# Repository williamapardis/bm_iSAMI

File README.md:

# iSAMI Bristlemouth Interface Firmware
This includes the firmware for the Bristlemouth development kit to interface a Sofar Smart Spotter Mooring with Sunburst Sensor's iSAMI-pH instrument. The frimware functions as follows:

* Bristlemouth Mote triggers a measurement on the iSAMI through the RS232 connection at a specified interval.
* The iSAMI runs through its measurment sequence (~60s) and transmits its raw hex data through the RS232 connection.
* This 233 byte hex code is proccessed and a series of calculations lead to the determination of pH.
* Raw hex data is stored on the Spotter SD card through the Bristlemouth network
* pH and external temperature are stored on the Spotter SD and transmitted over the cellular modem.

Check out the project on the [forum](https://bristlemouth.discourse.group/t/turn-key-coastal-ph-monitoring-with-spotter-bristlemouth-and-sunburst-sensor-s-isami-ph/489?u=wpardis).

## Dependencies
### Main Protocol
- BM Protocol v2.1.0
  - Repository: https://github.com/bristlemouth/bm_protocol.git

## Wiring of the iSAMI-pH to the Bristlemouth Dev Kit
Please note that I have secured the development board to the oposite endcap it comes pre installed on with the Dev. Kit. This lets us utilize the 2P Molex Microfit interconnect for assembly of the pressure vessel, rather than adding our own.
| Pin to Pin Discription | Example Image of termination |
|---------|---------|
| | |

# The Project
We're trying to put powerful chemistry in the hands of a wider demographic and lower the barrier to entry through standardized integration of well established oceanographic assets. 

This is the integration and deomonstraition of Sunburst Sensor’s iSAMI-pH and Sofar Ocean’s Smart Spotter Buoy through the Bristlemouth Dev. kit. The Spotter and the iSAMI are well paired economically/electromechanically. However, the high cost of custom engineering integration still limits these cost effective solutions. With the adoption of Bristlemouth we mitigate costly integration. This strategic development has the opportunity to open up coastal pH monitoring to a wider range of users through the turn-key operability of Sofar’s ecosystem. This ecosystem as a gateway to the demonstrated success of Sunburst Sensor’s spectrophotometric measurement approach enables a higher density of accurate and low drift pH observations in the ocean.

## How does the iSAMI-pH work?
Most people are familiar with litmus paper—strips containing pH-sensitive dye that change color when exposed to different solutions. The iSAMI-pH is essentially an automated version of litmus paper, but instead of visual observation, it mixes liquid dye with seawater and analyzes the color change using precise embedded optical electronics. We would call this a spectrophotometric pH method: spectro - (color), photo - (light), metric - (measuring). Here is the dye (m-Cresol Purple) in action:

The advantage of spectrophotometric pH is that, rather than taking a calibrated approach like electrodes, it directly measures hydrogen ions in solution. measure of hydrogen ions in solution. This calibration free method consequently has very low drift, allowing these sensors to dwell for years while maintaining their accuracy.
Thanks to the exacting work of analytical chemists, this dye’s physical properties have been scrutinized in the seawater matrix, making it highly accurate. It is considered the gold standard for quantitative oceanographic pH measurement.

Thanks to Sunburst Sensor’s engineering and attention to detail, we have instruments like the iSAMI-pH, which realistically bring this measurement into the real world ocean environment. Here is a nice [overview of Sunburst](https://youtu.be/aXZPkW4L6uA?si=S3U1Ic4FXqChgCz4) as they were working to compete in the Wendy Schmidt Ocean-X prize. An important note [Sunburst Sensor took first place](https://www.pmel.noaa.gov/news-story/wendy-schmidt-ocean-health-xprize-winners-announced#:~:text=Winning%20first%20place%20in%20both,each%20team%20took%20home%20%24250%2C000.) in both categories: Accuracy and affordability. 

## Why pH?
If you were to take a single drop of seawater from the central pacific and compare it to one 30 years ago there would be ~42 billion more hydrogen ions in that single drop. Increased carbon dioxide in our atmosphere reacts with our ocean producing hydrogen ions in solution and perturbing our ocean's fundamental chemistry. How do we conceptualize such large changes in hydrogen ion concentration? The practical answer is pH. pH compresses the wild extremes of hydrogen ion concentration into a tidy, 14-step logarithmic scale.

$$
pH = log_{10}([H^+]),\ \ \ \ [H^+] \equiv \text{Hydtrogen Ion Concentraition}
$$

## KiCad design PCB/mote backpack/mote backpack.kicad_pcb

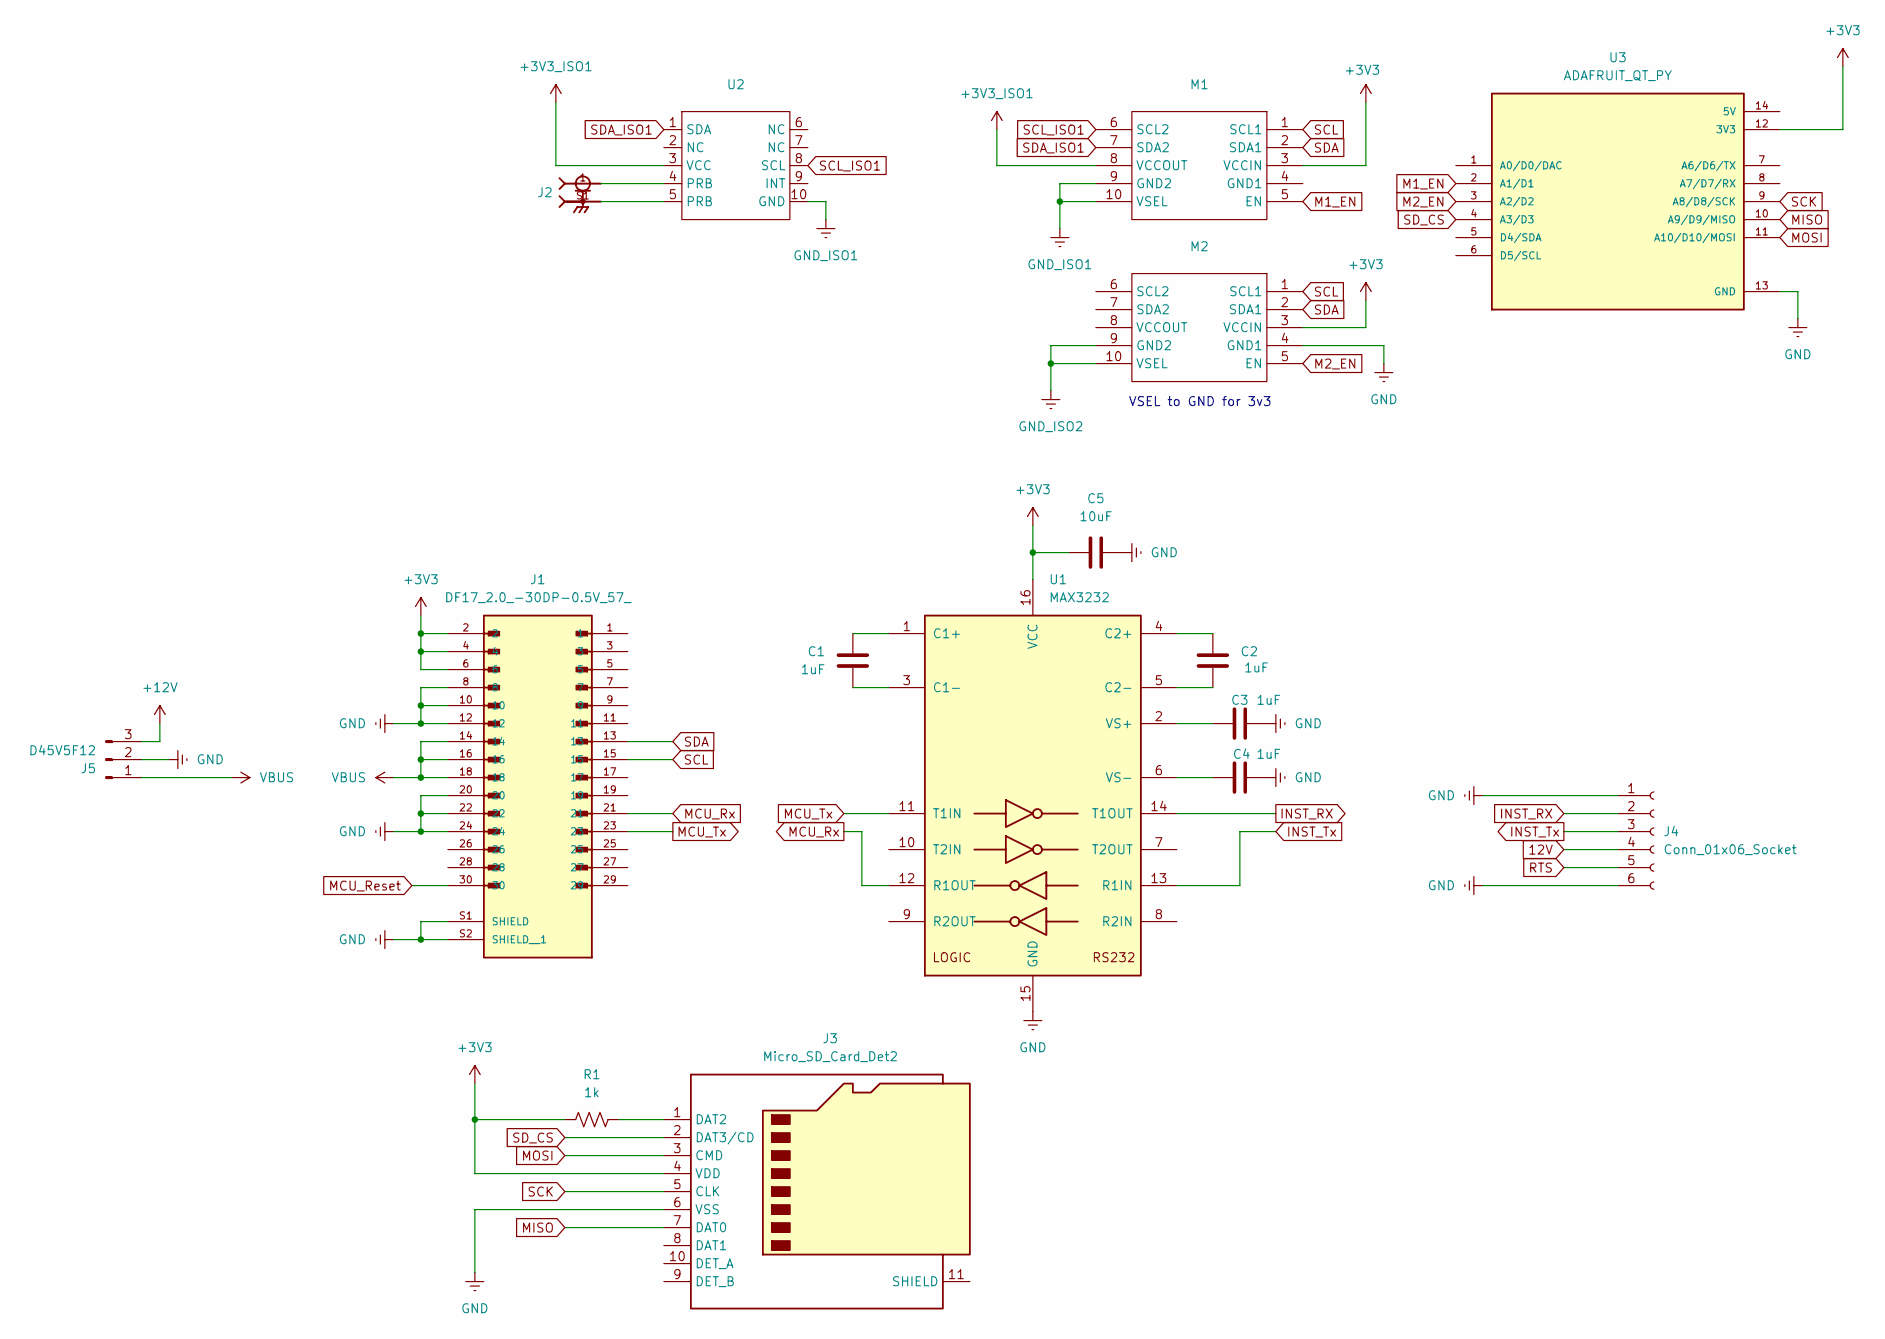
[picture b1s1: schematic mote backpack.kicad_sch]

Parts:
C1, C2, C3, C4: 1uF; C_0805_2012Metric
C5: 10uF; C_0805_2012Metric
J1: DF17_2.0_-30DP-0.5V_57_; HRS_DF17_2.0_-30DP-0.5V_57_
J2: 73251-1350; MOLEX_73251-1350; PARTREV C4
J3: Micro_SD_Card_Det2; microSD_HC_Molex_104031-0811
J4: Conn_01x06_Socket; PinHeader_1x06_P2.54mm_Vertical
J5: D45V5F12; PinHeader_1x03_P2.54mm_Vertical
M1, M2: Pololu Qwiic ISO
R1: 1k; R_0201_0603Metric_Pad0.64x0.40mm_HandSolder
U1: MAX3232; SOP65P640X120-16N
U2: conductivity OEM
U3: ADAFRUIT_QT_PY; MODULE_ADAFRUIT_QT_PY; PARTREV 2022-12-12

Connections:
12V: J4.4
+3V3: C5.2, J1.2, J1.4, J1.6, J3.4 (VDD), M1.3 (VCCIN), M2.3 (VCCIN), R1.1, U1.16 (VCC), U3.12 (3V3)
+3V3_ISO1: M1.8 (VCCOUT), U2.3 (VCC)
+12V: J5.3
GND: C3.1, C4.1, C5.1, J1.8, J1.10, J1.12, J1.20, J1.22, J1.24, J1.S1 (SHIELD), J1.S2 (SHIELD__1), J3.6 (VSS), J4.1, J4.6, J5.2, M2.4 (GND1), U1.15 (GND), U3.13 (GND)
GND_ISO1: M1.9 (GND2), M1.10 (VSEL), U2.10 (GND)
GND_ISO2: M2.9 (GND2), M2.10 (VSEL)
INST_RX: J4.2, U1.14 (T1OUT)
INST_Tx: J4.3, U1.13 (R1IN)
M1_EN: M1.5 (EN), U3.2 (A1/D1)
M2_EN: M2.5 (EN), U3.3 (A2/D2)
MCU_Reset: J1.30
MCU_Rx: J1.21, U1.12 (R1OUT)
MCU_Tx: J1.23, U1.11 (T1IN)
MISO: J3.7 (DAT0), U3.10 (A9/D9/MISO)
MOSI: J3.3 (CMD), U3.11 (A10/D10/MOSI)
unnamed: J2.1, U2.4 (PRB)
unnamed: J2.S1, U2.5 (PRB)
unnamed: J3.1 (DAT2), R1.2
unnamed: C1.2, U1.1 (C1+)
unnamed: C1.1, U1.3 (C1-)
unnamed: C2.2, U1.4 (C2+)
unnamed: C2.1, U1.5 (C2-)
unnamed: C3.2, U1.2 (VS+)
unnamed: C4.2, U1.6 (VS-)
RTS: J4.5
SCK: J3.5 (CLK), U3.9 (A8/D8/SCK)
SCL: J1.15, M1.1 (SCL1), M2.1 (SCL1)
SCL_ISO1: M1.6 (SCL2), U2.8 (SCL)
SDA: J1.13, M1.2 (SDA1), M2.2 (SDA1)
SDA_ISO1: M1.7 (SDA2), U2.1 (SDA)
SD_CS: J3.2 (DAT3/CD), U3.4 (A3/D3)
VBUS: J1.14, J1.16, J1.18, J5.1

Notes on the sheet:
VSEL to GND for 3v3

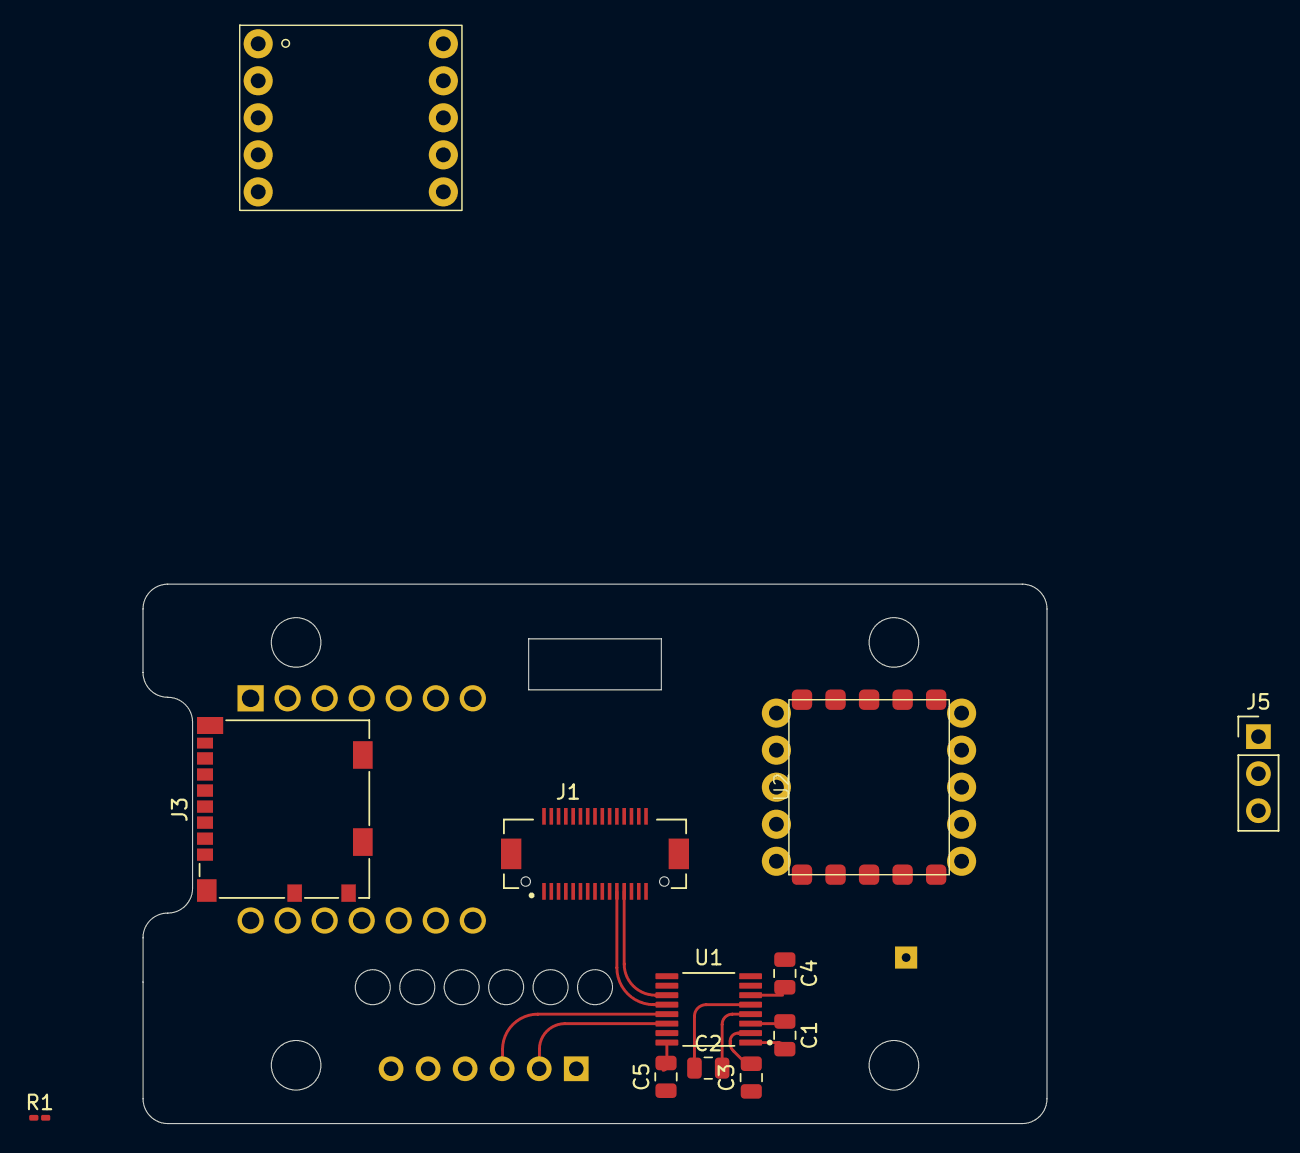
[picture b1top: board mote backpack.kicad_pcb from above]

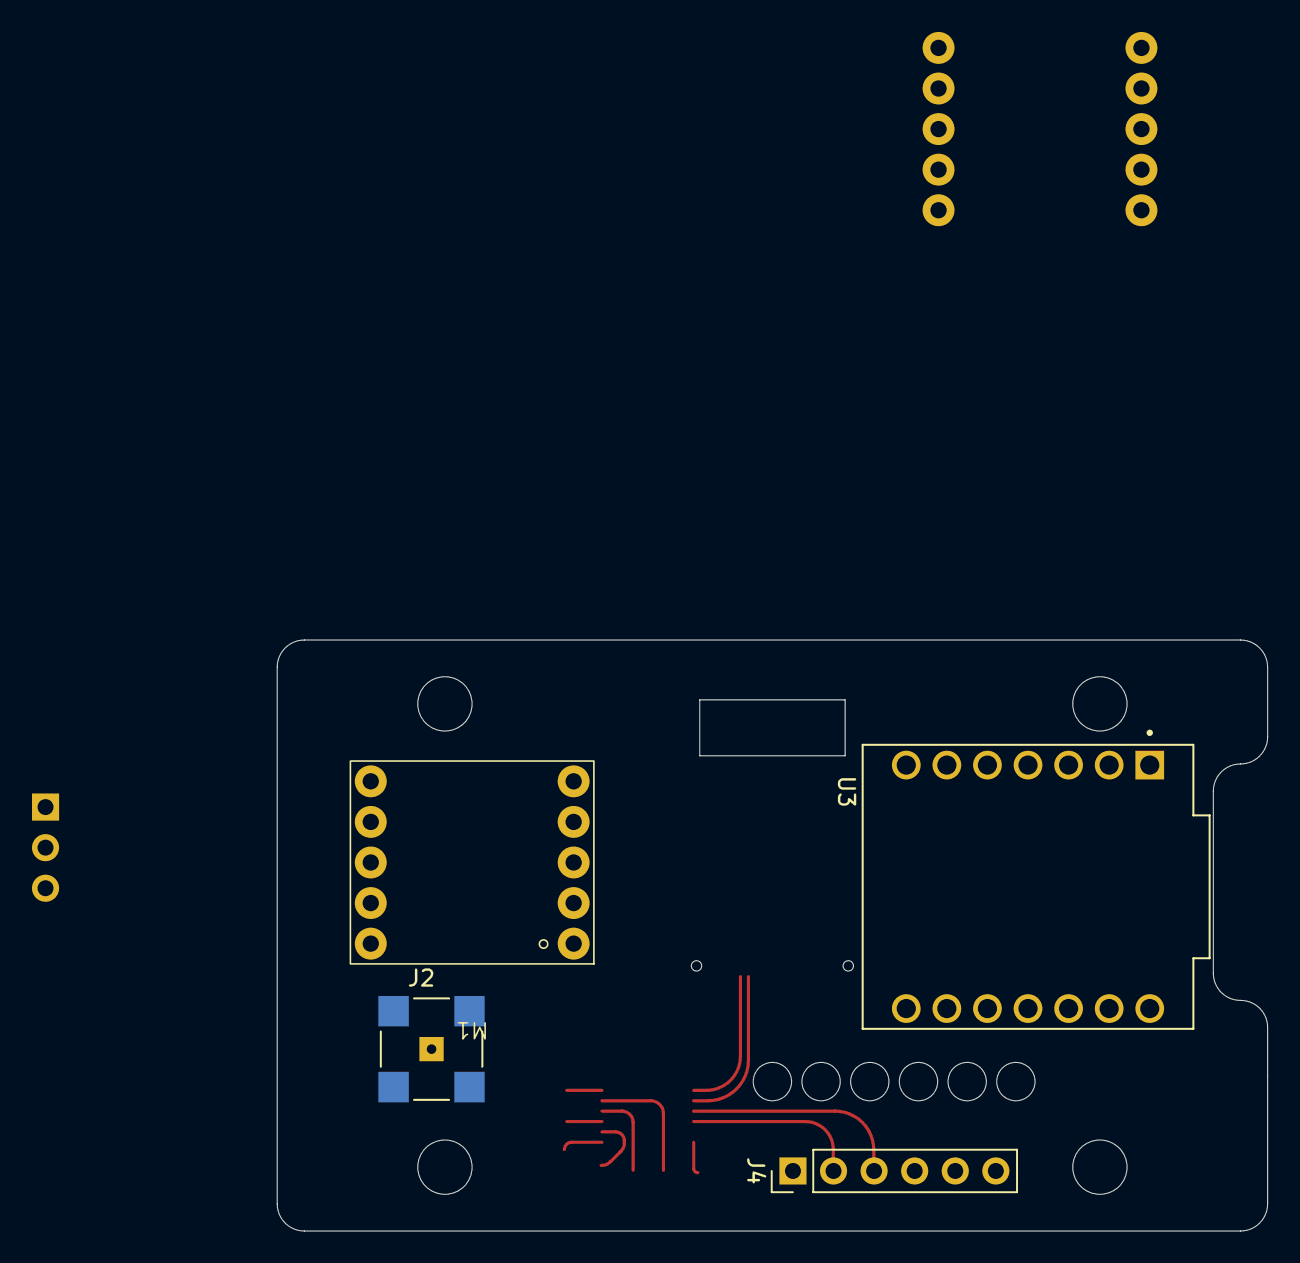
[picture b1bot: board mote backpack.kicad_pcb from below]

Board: 2 copper layers, 62.0 x 37.0 mm, 16 parts (4 on the bottom side), 29 nets.

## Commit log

2025-04-10 added sofar_tx and thier python decoder
2025-04-10 removing unnessisary decode script
2025-04-10 add a python script that uses Sofar API to import parse and decode data
2025-04-10 I have added a matplotlib plot of pH and Temperature
2025-04-12 set salinity to 28PPT for pier 28 and set the sampling frequency to 15min
2025-04-13 adding Sunburst Datasheets & Manuals
2025-04-16 added some notes from Jim to get the internal temperature right. primarily dividing by the R25 before stienhart. Still needs to be tested.
2025-04-16 added temperature compensation to the final pH
2025-04-16 remove py file
2025-04-19 plotting script
2025-05-02 first commit of mote carrier board PCB
2025-05-02 test that changes tracked
